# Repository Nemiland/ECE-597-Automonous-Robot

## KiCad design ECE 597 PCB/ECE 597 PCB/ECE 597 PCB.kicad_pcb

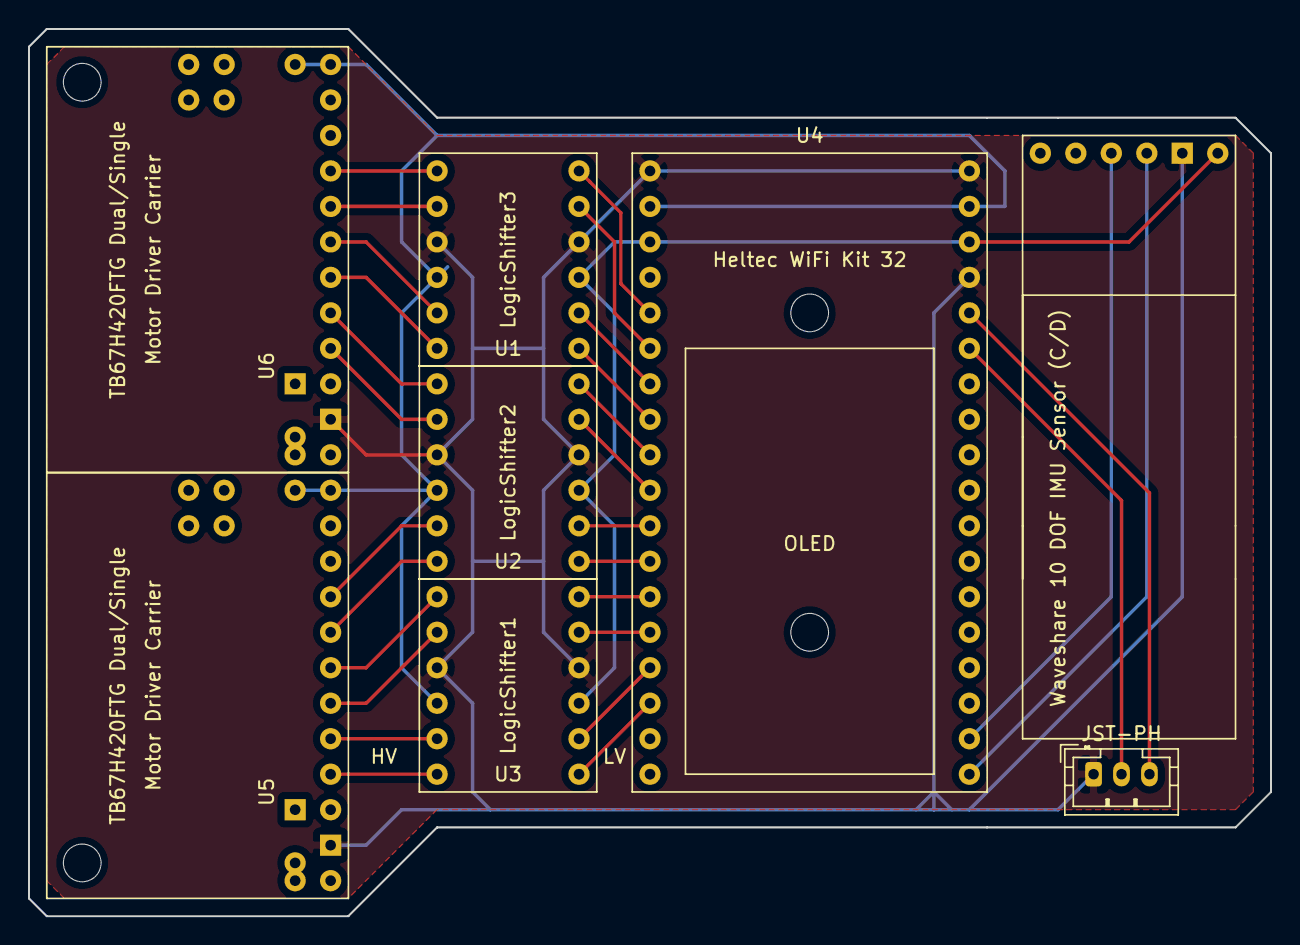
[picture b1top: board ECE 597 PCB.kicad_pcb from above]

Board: 2 copper layers, 88.9 x 63.5 mm, 12 parts (0 on the bottom side), 31 nets.

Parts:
JST-PH: Conn_01x03; JST_PH_B3B-PH-K_1x03_P2.00mm_Vertical
MK1, MK2, MK3, MK4: Mounting_Hole_PAD; MountingHole_2.7mm
U1: LogicShifter3; LogicShifter
U2: LogicShifter2; LogicShifter
U3: LogicShifter1; LogicShifter
U4: WiFiKit32
U5: MC1; MotCon
U6: MC2; MotCon
Waveshare 10 DOF IMU Sensor (C/D) : Waveshare10dof

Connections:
unnamed: JST-PH.1, U1.4, U1.9, U2.4, U2.9, U3.4, U3.9, U4.1, U4.33, U4.36, U5.1, U6.1, Waveshare 10 DOF IMU Sensor (C/D).5
unnamed: JST-PH.2, U4.31
unnamed: JST-PH.3, U4.32
unnamed: U1.1, U4.8
unnamed: U1.2, U4.7
unnamed: U1.3, U2.3, U3.3, U4.3, U4.34, Waveshare 10 DOF IMU Sensor (C/D).6
unnamed: U1.5, U4.6
unnamed: U1.6, U4.5
unnamed: U1.7, U6.8
unnamed: U1.8, U6.7
unnamed: U1.10, U2.10, U3.10, U4.2, U4.35, U5.11, U5.12, U6.11, U6.12
unnamed: U1.11, U6.6
unnamed: U1.12, U6.5
unnamed: U2.1, U4.12
unnamed: U2.2, U4.11
unnamed: U2.5, U4.10
unnamed: U2.6, U4.9
unnamed: U2.7, U6.4
unnamed: U2.8, U6.3
unnamed: U2.11, U5.8
unnamed: U2.12, U5.7
unnamed: U3.1, U4.16
unnamed: U3.2, U4.15
unnamed: U3.5, U4.14
unnamed: U3.6, U4.13
unnamed: U3.7, U5.6
unnamed: U3.8, U5.5
unnamed: U3.11, U5.4
unnamed: U3.12, U5.3
unnamed: U4.19, Waveshare 10 DOF IMU Sensor (C/D).4
unnamed: U4.20, Waveshare 10 DOF IMU Sensor (C/D).3

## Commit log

2019-07-12 7/12 Update - Added code for ESP32 WiFi Kit
2019-07-16 Added ROS framework
2019-08-08 8/8 - Fixed Typo
